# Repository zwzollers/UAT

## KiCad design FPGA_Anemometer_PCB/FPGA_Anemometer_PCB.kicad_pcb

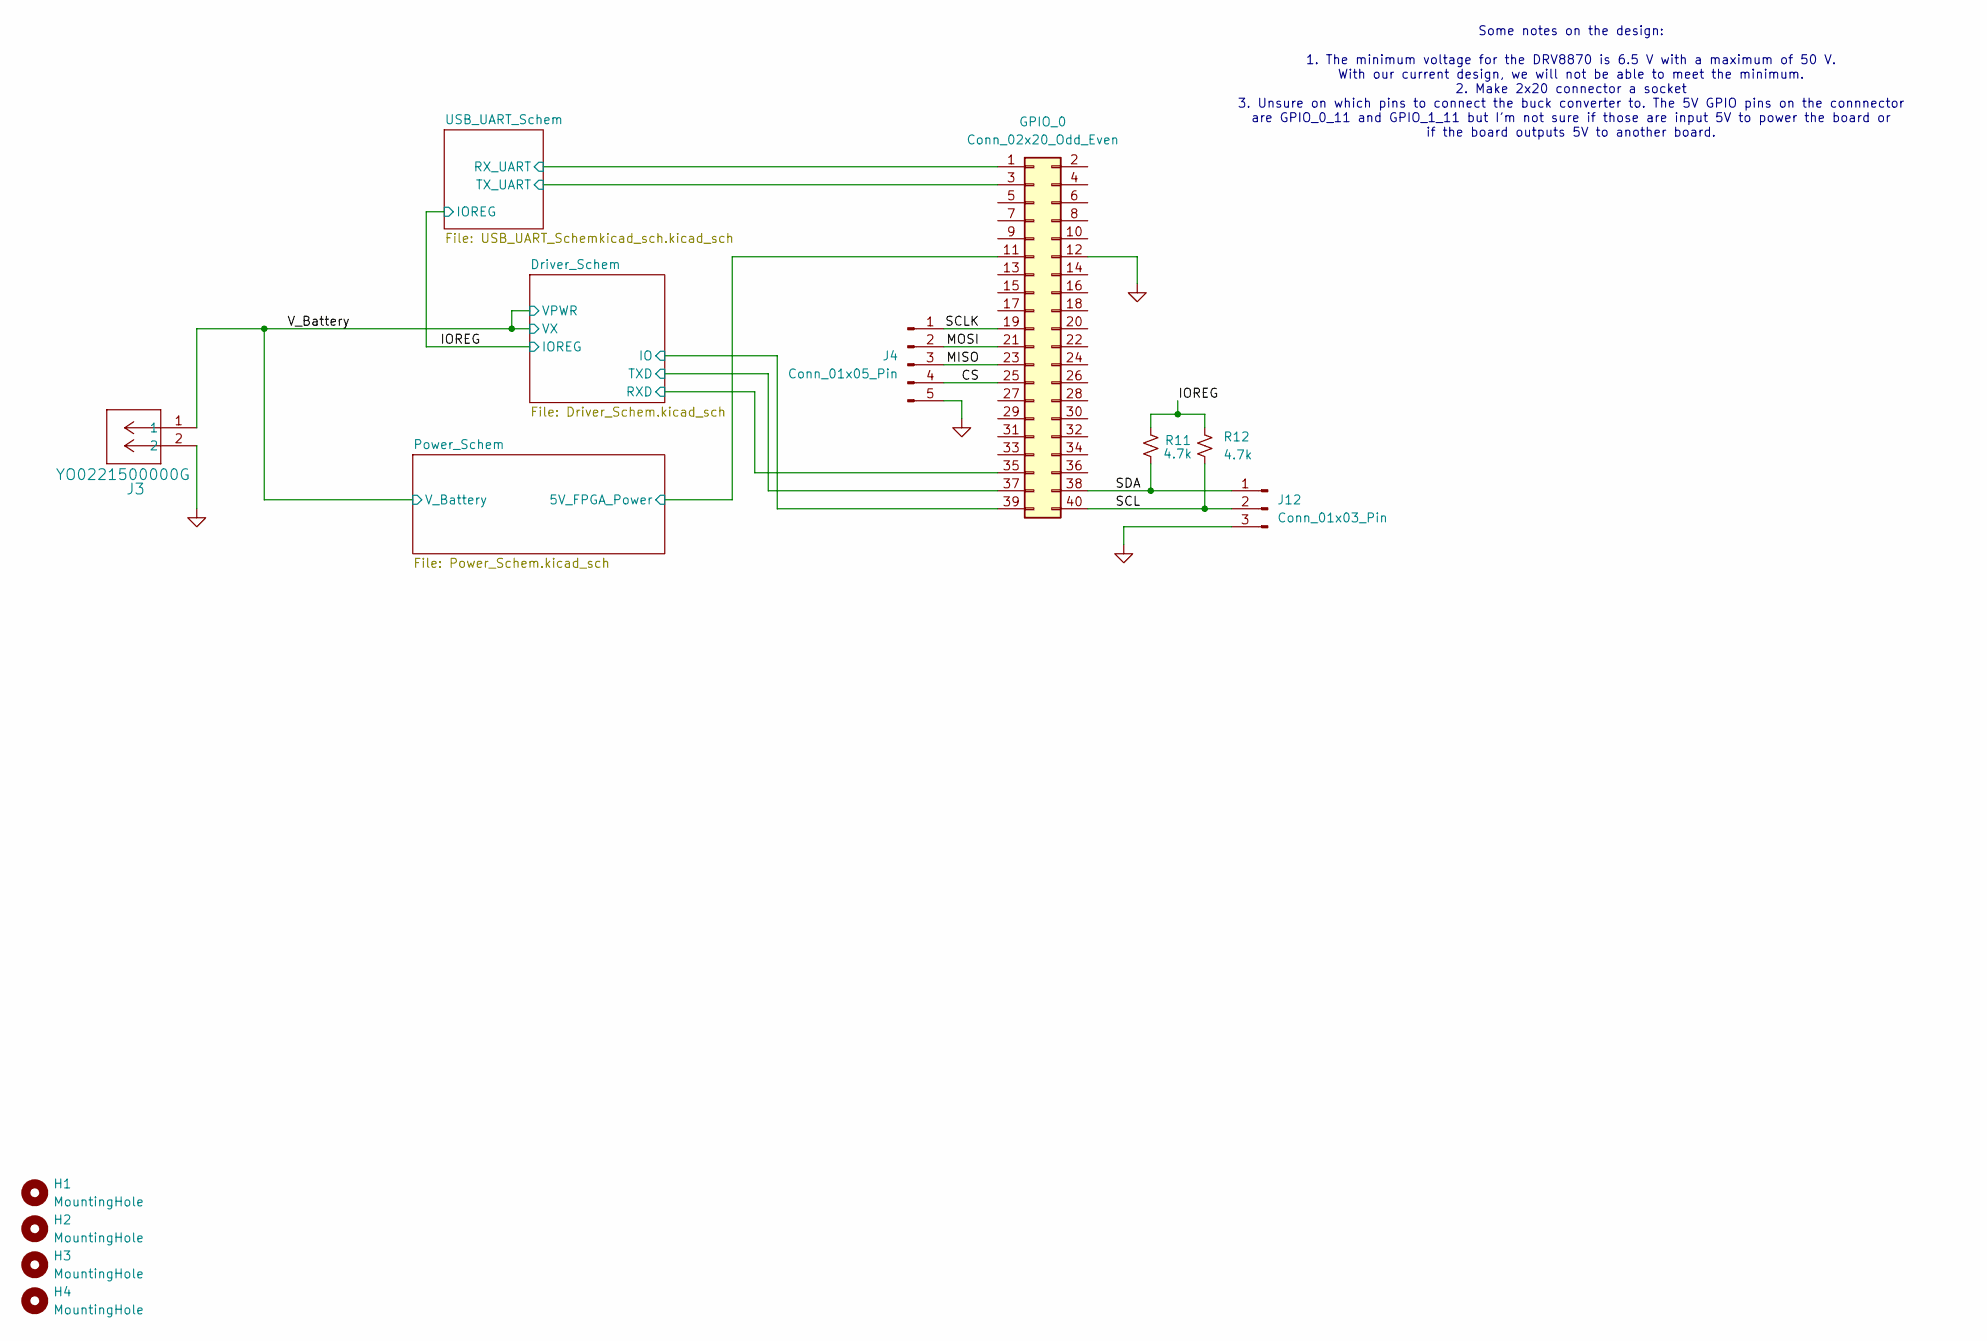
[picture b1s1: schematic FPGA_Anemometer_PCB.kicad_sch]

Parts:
GPIO_0: Conn_02x20_Odd_Even; PinSocket_2x20_P2.54mm_Vertical
H1, H2, H3, H4: MountingHole; MountingHole_3.2mm_M3
J3: YO0221500000G; CONN_YO0221500000G_AMP
J4: Conn_01x05_Pin; PinHeader_1x05_P2.54mm_Vertical
J12: Conn_01x03_Pin; PinHeader_1x03_P2.54mm_Vertical
R11, R12: 4.7k; R_0805_2012Metric

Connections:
/CS: GPIO_0.25, J4.4
/Driver_Schem/IO: GPIO_0.39; also elsewhere on the board
/Driver_Schem/RXD: GPIO_0.35; also elsewhere on the board
/Driver_Schem/TXD: GPIO_0.37; also elsewhere on the board
/IOREG: R11.1, R12.1; also elsewhere on the board
/MISO: GPIO_0.23, J4.3
/MOSI: GPIO_0.21, J4.2
/Power_Schem/5V_FPGA_Power: GPIO_0.11; also elsewhere on the board
/SCL: GPIO_0.40, J12.2, R12.2
/SCLK: GPIO_0.19, J4.1
/SDA: GPIO_0.38, J12.1, R11.2
/USB_UART_Schem/RXD: GPIO_0.1; also elsewhere on the board
/USB_UART_Schem/TXD: GPIO_0.3; also elsewhere on the board
/V_Battery: J3.1; also elsewhere on the board
GND: GPIO_0.12, J3.2, J4.5, J12.3; also elsewhere on the board

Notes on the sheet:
Some notes on the design: 1. The minimum voltage for the DRV8870 is 6.5 V with a maximum of 50 V. With our current design, we will not be able to meet the minimum. 2. Make 2x20 connector a socket 3. Unsure on which pins to connect the buck converter to. The 5V GPIO pins on the connnector are GPIO_0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

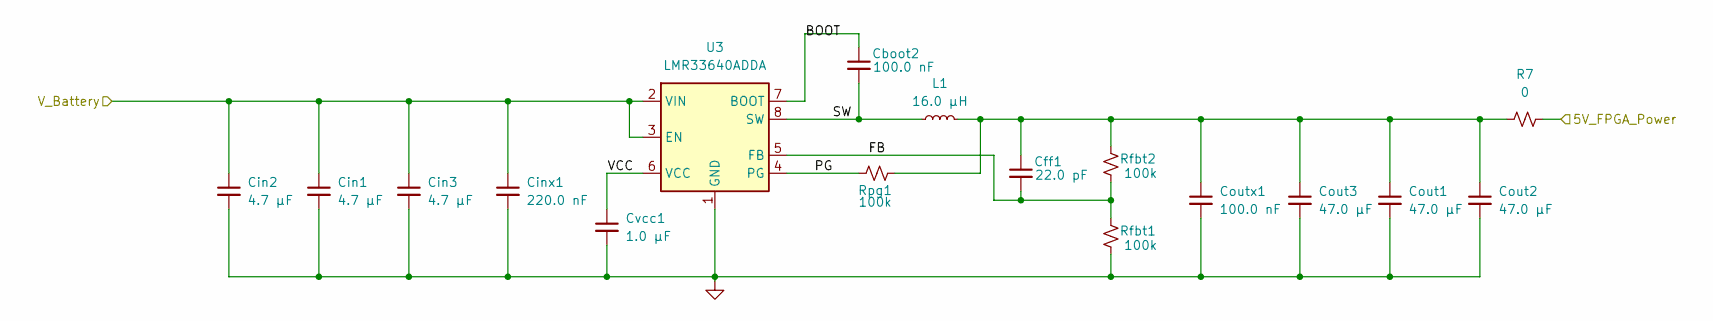
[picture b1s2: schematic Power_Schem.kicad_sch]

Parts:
Cboot2: 100.0 nF; C_0805_2012Metric
Cff1: 22.0 pF; C_0805_2012Metric
Cin1, Cin2, Cin3: 4.7 µF; C_0805_2012Metric
Cinx1: 220.0 nF; C_0805_2012Metric
Cout1, Cout2, Cout3: 47.0 µF; C_0805_2012Metric
Coutx1: 100.0 nF; C_0805_2012Metric
Cvcc1: 1.0 µF; C_0805_2012Metric
L1: 16.0 µH; IND_SRP1038A_BRN
R7: 0; R_0805_2012Metric
Rfbt1, Rfbt2: 100k; R_0805_2012Metric
Rpg1: 100k; R_0805_2012Metric
U3: LMR33640ADDA; Texas_HSOP-8-1EP_3.9x4.9mm_P1.27mm_ThermalVias

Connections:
/Power_Schem/5V_FPGA_Power: R7.2; also elsewhere on the board
/Power_Schem/BOOT: Cboot2.1, U3.7 (BOOT)
/Power_Schem/FB: Cff1.2, Rfbt1.2, Rfbt2.1, U3.5 (FB)
/Power_Schem/PG: Rpg1.1, U3.4 (PG)
/Power_Schem/SW: Cboot2.2, L1.1, U3.8 (SW)
/Power_Schem/VCC: Cvcc1.1, U3.6 (VCC)
/V_Battery: Cin1.1, Cin2.1, Cin3.1, Cinx1.1, U3.2 (VIN), U3.3 (EN); also elsewhere on the board
GND: Cin1.2, Cin2.2, Cin3.2, Cinx1.2, Cout1.2, Cout2.2, Cout3.2, Coutx1.2, Cvcc1.2, Rfbt1.1, U3.1 (GND), U3.9 (GND); also elsewhere on the board
unnamed: Cff1.1, Cout1.1, Cout2.1, Cout3.1, Coutx1.1, L1.2, R7.1, Rfbt2.2, Rpg1.2

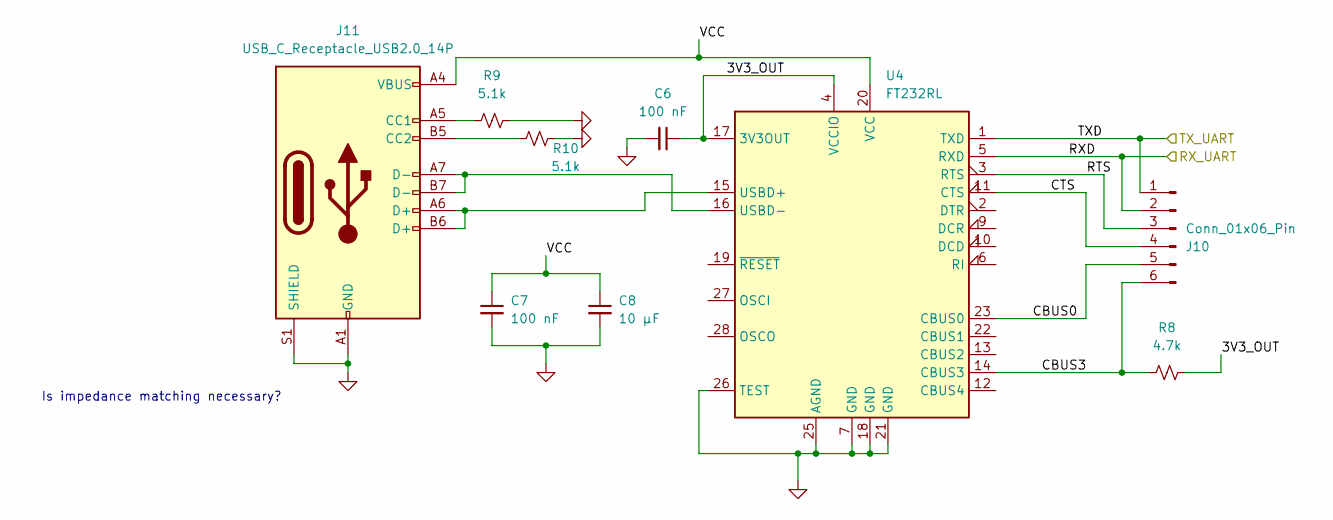
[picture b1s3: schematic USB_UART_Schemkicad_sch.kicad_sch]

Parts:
C6, C7: 100 nF; C_0805_2012Metric
C8: 10 µF; C_0805_2012Metric
J10: Conn_01x06_Pin; PinHeader_1x06_P2.54mm_Vertical
J11: USB_C_Receptacle_USB2.0_14P; USB_C_Receptacle_GCT_USB4110
R8: 4.7k; R_0805_2012Metric
R9, R10: 5.1k; R_0805_2012Metric
U4: FT232RL; SSOP-28_5.3x10.2mm_P0.65mm

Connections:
/USB_UART_Schem/3V3_OUT: C6.1, R8.2, U4.4 (VCCIO), U4.17 (3V3OUT)
/USB_UART_Schem/CBUS0: J10.5, U4.23 (CBUS0)
/USB_UART_Schem/CBUS3: J10.6, R8.1, U4.14 (CBUS3)
/USB_UART_Schem/CTS: J10.4, U4.11 (CTS)
/USB_UART_Schem/RTS: J10.3, U4.3 (RTS)
/USB_UART_Schem/RXD: J10.2, U4.5 (RXD); also elsewhere on the board
/USB_UART_Schem/TXD: J10.1, U4.1 (TXD); also elsewhere on the board
/USB_UART_Schem/VCC: C7.1, C8.1, J11.A4 (VBUS), J11.A9 (VBUS), J11.B4 (VBUS), J11.B9 (VBUS), U4.20 (VCC)
GND: C6.2, C7.2, C8.2, J11.A1 (GND), J11.A12 (GND), J11.B1 (GND), J11.B12 (GND), J11.S1 (SHIELD), R9.1, R10.1, U4.7 (GND), U4.18 (GND), U4.21 (GND), U4.25 (AGND), U4.26 (TEST); also elsewhere on the board
unnamed: J11.A5 (CC1), R9.2
unnamed: J11.B5 (CC2), R10.2
unnamed: J11.A6 (D+), J11.B6 (D+), U4.15 (USBD+)
unnamed: J11.A7 (D-), J11.B7 (D-), U4.16 (USBD-)

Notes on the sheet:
Is impedance matching necessary?

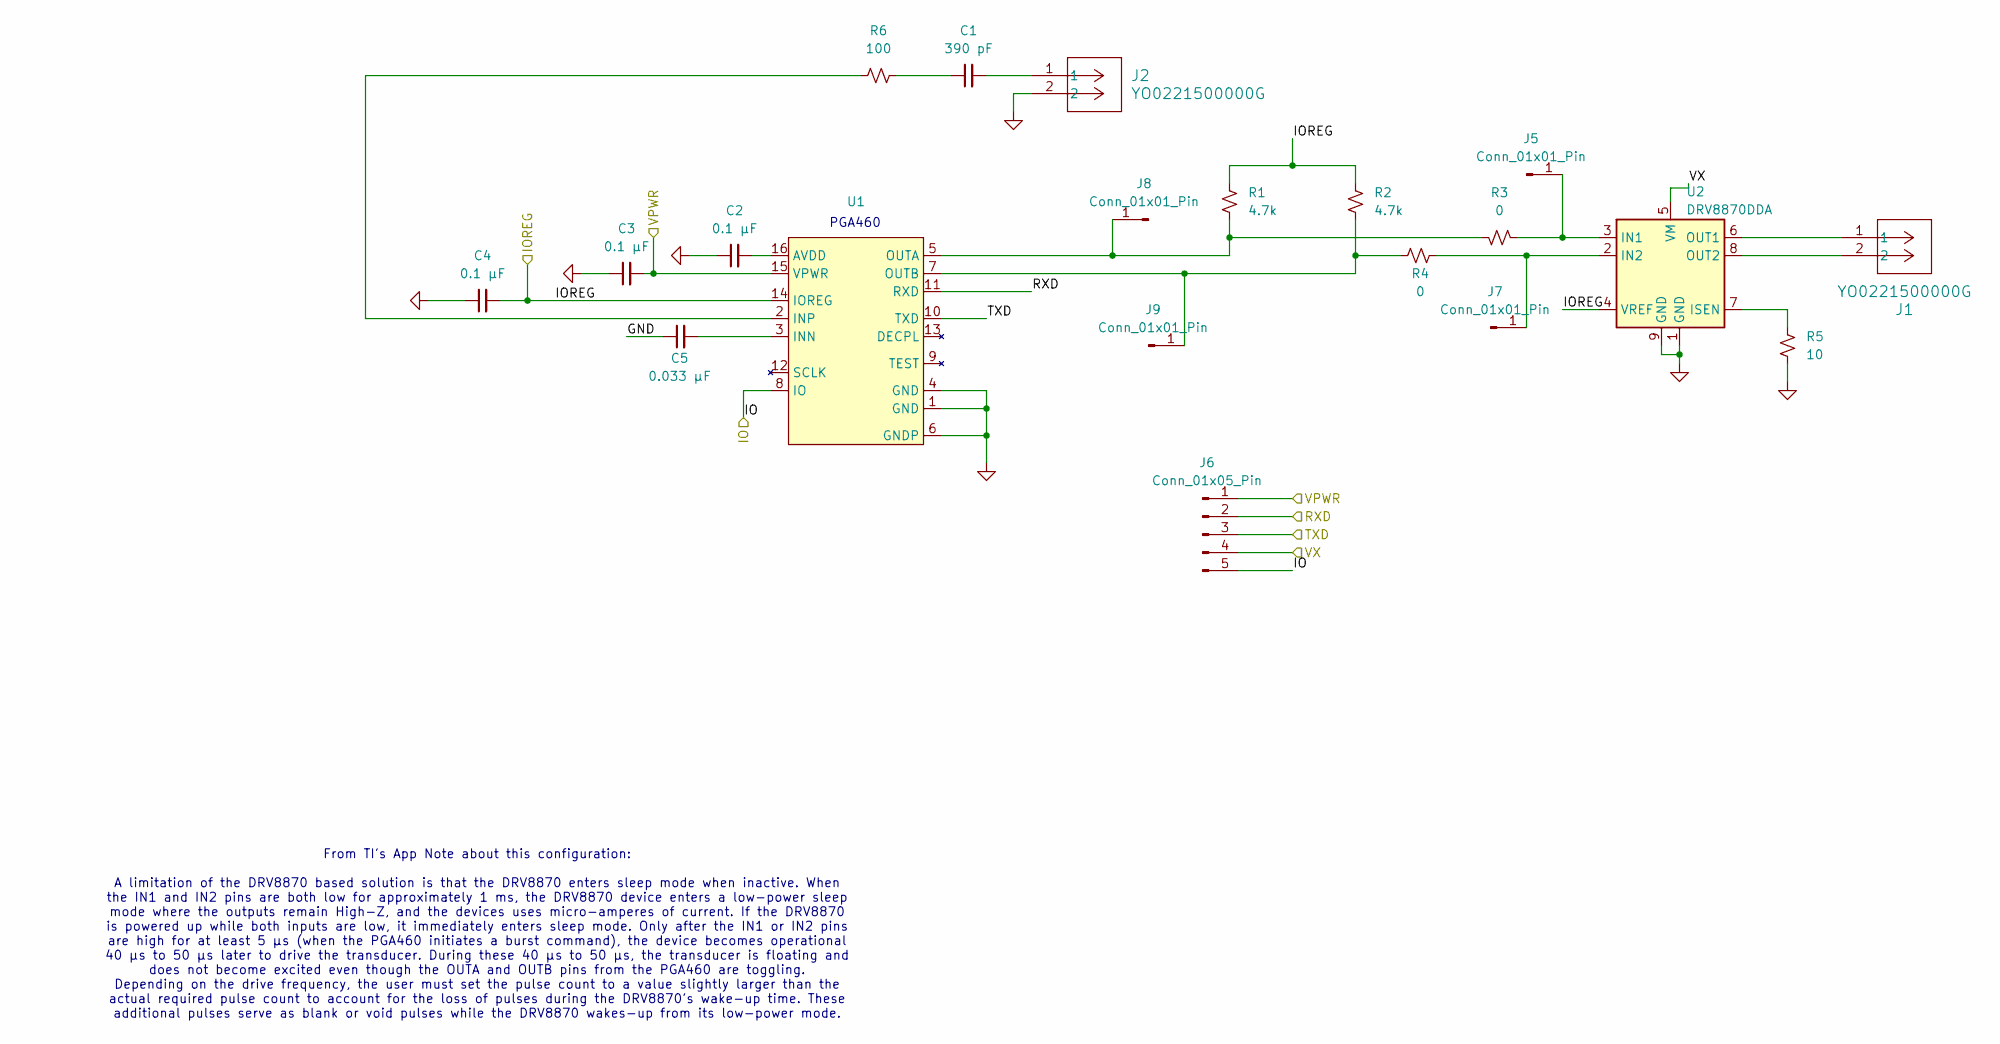
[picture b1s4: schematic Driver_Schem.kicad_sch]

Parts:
C1: 390 pF; C_0805_2012Metric
C2, C3, C4: 0.1 µF; C_0805_2012Metric
C5: 0.033 µF; C_0805_2012Metric
J1, J2: YO0221500000G; CONN_YO0221500000G_AMP
J5, J7, J8, J9: Conn_01x01_Pin; PinHeader_1x01_P2.54mm_Vertical
J6: Conn_01x05_Pin; PinHeader_1x05_P2.54mm_Vertical
R1, R2: 4.7k; R_0805_2012Metric
R3, R4: 0; R_0805_2012Metric
R5: 10; R_0805_2012Metric
R6: 100; R_0805_2012Metric
U1: PW16_TEX
U2: DRV8870DDA; Texas_HTSOP-8-1EP_3.9x4.9mm_P1.27mm_EP2.95x4.9mm_Mask2.4x3.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

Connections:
/Driver_Schem/IO: J6.5, U1.8 (IO); also elsewhere on the board
/Driver_Schem/RXD: J6.2, U1.11 (RXD); also elsewhere on the board
/Driver_Schem/TXD: J6.3, U1.10 (TXD); also elsewhere on the board
/IOREG: C4.2, R1.1, R2.1, U1.14 (IOREG), U2.4 (VREF); also elsewhere on the board
/V_Battery: C3.2, J6.1, J6.4, U1.15 (VPWR), U2.5 (VM); also elsewhere on the board
GND: C2.1, C3.1, C4.1, C5.1, J2.2, R5.2, U1.1 (GND), U1.4 (GND), U1.6 (GNDP), U2.1 (GND), U2.9 (GND); also elsewhere on the board
unnamed: C1.1, R6.2
unnamed: C1.2, J2.1
unnamed: J5.1, R3.1, U2.3 (IN1)
unnamed: J7.1, R4.2, U2.2 (IN2)
unnamed: J8.1, R1.2, R3.2, U1.5 (OUTA)
unnamed: J9.1, R2.2, R4.1, U1.7 (OUTB)
unnamed: C2.2, U1.16 (AVDD)
unnamed: C5.2, U1.3 (INN)
unnamed: R6.1, U1.2 (INP)
unnamed: R5.1, U2.7 (ISEN)
unnamed: J1.1, U2.6 (OUT1)
unnamed: J1.2, U2.8 (OUT2)

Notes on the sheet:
From TI's App Note about this configuration: A limitation of the DRV8870 based solution is that the DRV8870 enters sleep mode when inactive. When the IN1 and IN2 pins are both low for approximately 1 ms, the DRV8870 device enters a low-power sleep mode where the outputs remain High-Z, and the devic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
PGA460

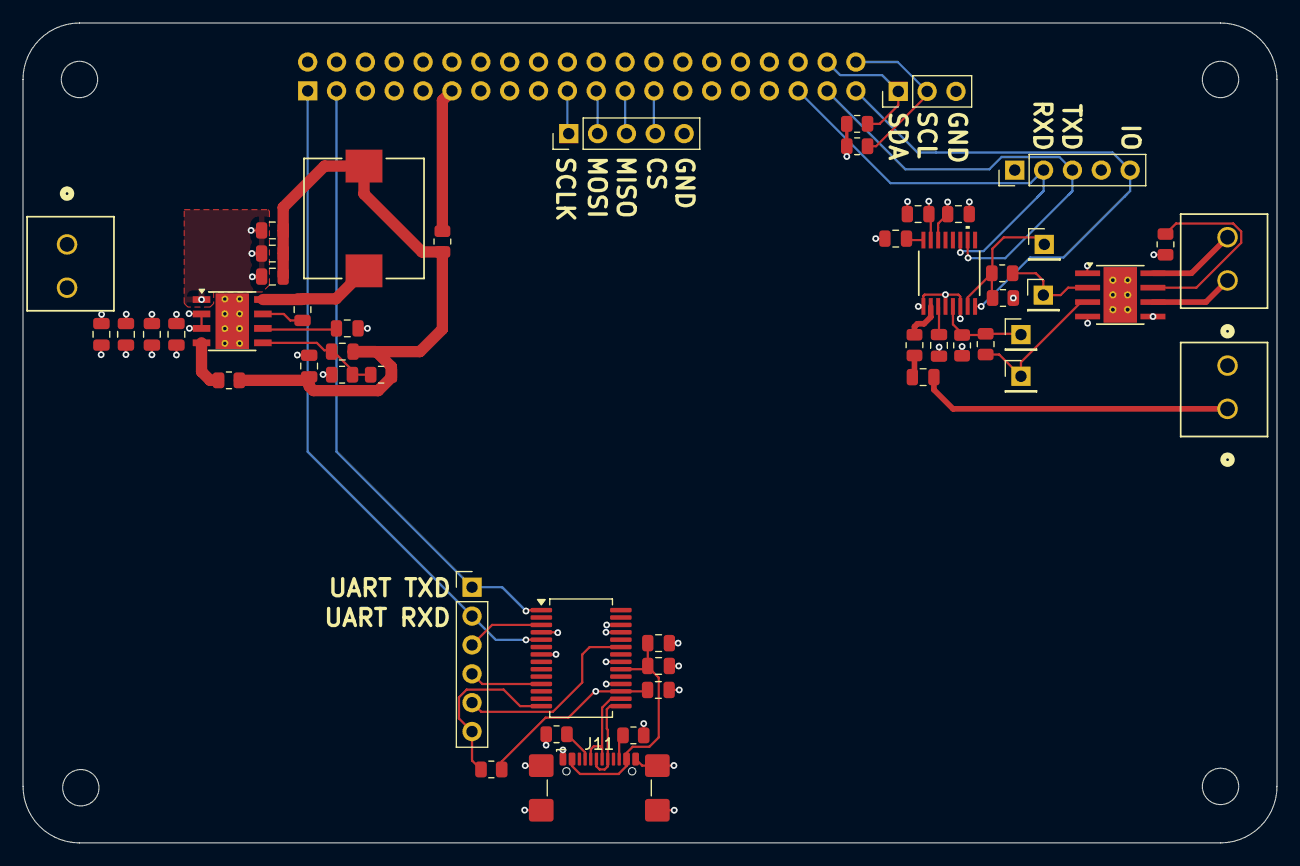
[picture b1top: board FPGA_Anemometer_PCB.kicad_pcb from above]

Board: 4 copper layers, 110.4 x 72.2 mm, 56 parts (1 on the bottom side), 43 nets.

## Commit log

2026-01-20 init
2026-01-25 Add files via upload
    If downloading, there may be an issue with not being able to open the schematic or PCB editor. If that is the case, let me know and I will upload both of the files.
    The other two files are a symbol and footprint of the connector.
2026-01-28 Add files via upload
    New changes to the PCB
2026-02-01 Add files via upload
    This is the current PCB design. I am open to suggestions for changes.
2026-02-01 Add files via upload
    This will be the most up to date PCB. Throw the 3D viewer on and rotate it for an easter egg.
2026-02-02 Add files via upload
    PCB commit
2026-02-02 added SPI module
2026-02-09 Added testbench and fixed syntax errors in SPI.v
2026-02-09 Revert "Added testbench and fixed syntax errors in SPI.v"
    This reverts commit fdf194f347b0a5dca48e437416eb849c79a4274f.
2026-02-09 Removed SPI folder from main
2026-02-09 Added Testbench and fixed errors in SPI.v
2026-02-10 added uart and cleanup
2026-02-10 updated pcb
2026-04-08 Added LCD Driver Module
2026-04-20 Updated with working LCD controller that displays speed in first row and direction in second row.
2026-04-22 Included LCD_Test module
2026-04-23 working ping sensor and started merging all modules into a single top level file
2026-05-01 Added SD Card files
2026-05-12 finished
